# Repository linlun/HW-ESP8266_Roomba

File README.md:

# HW-ESP8266_Roomba
Kicad schematics of a generic ESP8266 board with interfaces for OLED-display, rotary encoder, Roomba and DC/DC

Make shore that the latest kicad libraries are installed at: C:\Program Files\KiCad\share\kicad
Download from https://github.com/KiCad/kicad-library adn extract in the folder above if not.

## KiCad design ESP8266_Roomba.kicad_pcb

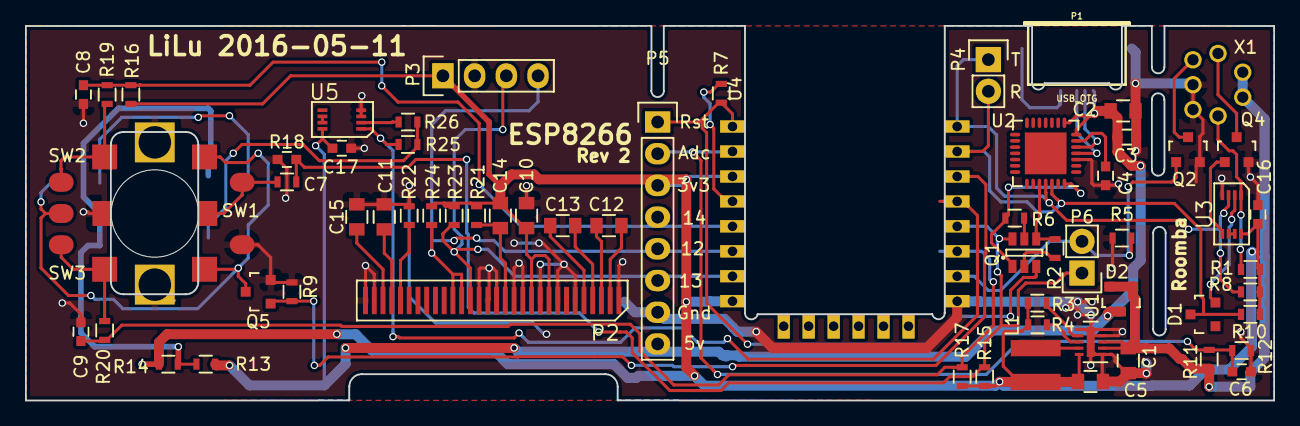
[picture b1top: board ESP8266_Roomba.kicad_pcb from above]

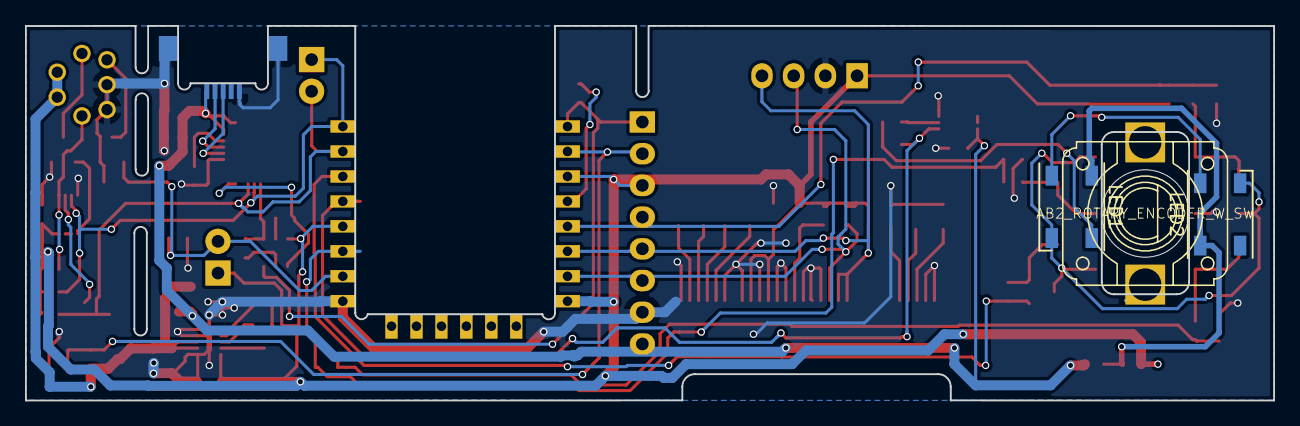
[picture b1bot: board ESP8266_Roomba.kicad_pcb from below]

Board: 2 copper layers, 100.0 x 30.0 mm, 68 parts (3 on the bottom side), 50 nets.

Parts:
C1, C11, C14, C15: 2u2; C_0805
C2, C10, C12, C13: 1u; C_0805
C3, C4, C6, C7, C8, C9, C16, C17: 100n; C_0603
C5: 22u; C_0805
D1, D2: MMBD717LT1G; SOT-23
L1: VLS4012ET-100M
LED1, LED2: WS2812B; LED_WS2812B-PLCC4
P1: USB_OTG; conn_usb_B_micro_smd-backside
P2: UG_62864
P3: CONN_01X04; Pin_Header_Straight_1x04
P4, P6: CONN_01X02; Pin_Header_Straight_1x02
P5: CONN_01X08; Pin_Header_Straight_1x08
Q1: DMC204010R; SOT-23-6
Q2, Q4, Q5: 2N7002; SOT-23
R1: 1M; R_0603
R2, R6, R7, R15, R16, R17, R21, R23, R24: 10k; R_0603
R3, R4, R5, R8, R9, R10: 100k; R_0603
R11: 470k; R_0603
R12: 18k; R_0603
R13, R14, R25, R26: 0R; R_0603
R18, R19, R20: 1k; R_0603
R22: 390k; R_0603
ROT_ENC1: AB2_ROTARY_ENCODER_W_SW; ROT_ENC_backside
SW1, SW2, SW3: SW_PUSH; switch3x6_smd
U1: TPS62177; DFN-10-1EP_2x3mm_Pitch0.5mm
U2: CP2102; QFN-28-1EP_5x5mm_Pitch0.5mm
U3, U5: 74LVC3G14; VSSOP-8
U4: ESP-12E; ESP-12E_SideMounted
X1: MINI_DIN_7; MiniDin-7

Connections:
+3V3: C5.1, C10.1, C14.1, C16.1, L1.2, P2.9, P2.11, P3.1, P5.3, R1.2, R3.1, R4.1, R8.1, R10.1, R14.1, R15.2, R16.2, R17.2, R21.2, R23.2, R24.2, U1.10, U3.8, U4.8
+12V: C1.1, D2.1, D2.2, R11.1, U1.2, U1.3, X1.1, X1.2
/5V: C2.1, C3.1, C17.1, D2.3, P1.1, P5.8, R13.2, U2.7, U2.8, U5.8
/ADC: C6.1, P5.2, R11.2, R12.1, U4.2
/DTR: Q1.1, R6.1, U2.28
/Enc_A: C9.1, R17.1, R20.2, U4.17
/Enc_B: C8.1, P5.4, R16.1, R19.2, U4.5
/LED: R25.2, U4.19, U5.1
/PowerOn: Q5.1, R9.2, U4.20
/RST: P5.1, Q1.3, R7.2, U4.1
/RTS: Q1.4, R2.1, U2.24
/RXD: D1.3, P4.2, R10.2, U2.26, U4.21
/Roomba_Wake: P6.2, Q2.1, R5.2, U4.16
/SCL: P2.18, P3.3, P5.6, R23.1, U4.7
/SDA: P2.19, P2.20, P3.4, P5.5, R24.1, U4.6
/Switch: C7.1, P6.1, Q1.6, R15.1, R18.2, U4.18
/TXD: P4.1, R8.2, U2.25, U3.3, U4.22
GND: C1.2, C2.2, C3.2, C4.2, C5.2, C6.2, C7.2, C8.2, C9.2, C11.2, C14.2, C15.2, C16.2, C17.2, P1.5, P1.6, P2.1, P2.6, P2.8, P2.10, P2.12, P2.13, P2.15, P2.16, P2.17, P2.29, P2.30, P3.2, P5.7, Q2.2, Q4.2, Q5.2, R5.1, R9.1, R12.2, R22.2, ROT_ENC1.6, ROT_ENC1.7, SW1.2, U1.1, U1.4, U1.5, U1.6, U1.11, U2.3, U3.4, U4.15, U5.3, U5.4, X1.6, X1.7
GNDPWR: LED1.3, LED2.3, Q5.3, ROT_ENC1.2, SW2.2, SW3.2
unnamed: C4.1, U2.6
unnamed: C10.2, P2.14, R21.1
unnamed: C11.1, P2.27
unnamed: C12.1, P2.2
unnamed: C12.2, P2.3
unnamed: C13.1, P2.4
unnamed: C13.2, P2.5
unnamed: C15.1, P2.28
unnamed: D1.2, U3.2
unnamed: L1.1, U1.9
unnamed: LED1.1, LED2.1, R13.1, R14.2
unnamed: LED1.2, LED2.4
unnamed: LED1.4, R25.1, R26.1
unnamed: P1.2, U2.5
unnamed: P1.3, U2.4
unnamed: P2.26, R22.1
unnamed: Q1.2, R2.2
unnamed: Q1.5, R6.2
unnamed: Q2.3, X1.5
unnamed: Q4.1, U3.5
unnamed: Q4.3, X1.3
unnamed: R1.1, U3.1, X1.4
unnamed: R3.2, U1.7
unnamed: R4.2, U1.8
unnamed: R7.1, U4.4
unnamed: R18.1, ROT_ENC1.4, SW1.1
unnamed: R19.1, ROT_ENC1.3, SW2.1
unnamed: R20.1, ROT_ENC1.1, SW3.1
unnamed: R26.2, U5.2
unnamed: U3.6, U3.7
unnamed: U5.6, U5.7

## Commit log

2016-04-30 Started project
2016-04-30 more components added to schematic
2016-05-02 Added alot of footprints
2016-05-03 all footprints added
2016-05-03 some layout done
2016-05-09 more layout done
2016-05-10 layout done
2016-05-10 Finished, commit before creating a panel
2016-05-10 Added gerber output for panel with 3 boards
2016-05-11 Revision 2 Fixed faulty footprint for diodes added partnumbers for more components calculated voltage devider for adc
2016-06-16 Added output BOM with some links to digikey
